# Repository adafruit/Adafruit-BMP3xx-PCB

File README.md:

## Adafruit BMP3xx - Precision Barometric Pressure and Altimeter PCB

<a href="http://www.adafruit.com/products/3966"><br/>
<a href="http://www.adafruit.com/products/3966"><br/>
<a href="http://www.adafruit.com/products/4816"><br/>
Click here to purchase one from the Adafruit shop</a>

PCB files for the Adafruit BMP388 - Precision Barometric Pressure and Altimeter. Format is EagleCAD schematic and board layout
* https://www.adafruit.com/product/3966
* https://www.adafruit.com/product/4816

### Description

Bosch has been a leader in barometric pressure sensors, from the [BMP085](https://www.adafruit.com/product/1603), [BMP180](https://www.adafruit.com/product/1603), and [BMP280](https://www.adafruit.com/product/2651)... now we've got the next generation, the **Adafruit BMP3xx Precision Barometric Pressure sensor**. As you would expect, this sensor is similar to its earlier versions but even better. The BMP388 has better precision than ever, which makes it excellent for environmental sensing or as a **precision altimeter**. It can even be used in either I2C and SPI configurations.

The BMP388 is the next-generation of sensors from Bosch, and is the upgrade to the BMP280 - with a low altitude noise as low as 0.1m and the same fast conversion time. And like the previous BMP280, you can use I2C or SPI. For simple easy wiring, go with I2C. If you want to connect a bunch of sensors without worrying about I2C address collisions, go with SPI.

The BMP390 is the next-generation of sensors from Bosch and is the upgrade to the BMP280 and BMP388 - with a low-altitude noise as low as 0.1m and the same fast conversion time. And like the previous BMP280, you can use I2C or SPI. For simple easy wiring, go with I2C. If you want to connect a bunch of sensors without worrying about I2C address collisions, go with SPI.

This sensor has a relative accuracy of 8 Pascals, which translates to about ± 0.5 meter of altitude (compare to the BMP280's 12 Pascal/ ±1 meter). The datasheet sort of implies they intend this sensor to be used for drones and quadcopters, to keep altitude stable, but you could also use this for wearables or any project that wants to track height-above-sea-level. Note that for absolute height you'll still need to enter in the barometric pressure at sea level, if the weather changes, but that's true of every altimeter sensor that uses pressure. You can also measure temperature with ±0.5°C accuracy.

Nice sensor right? So we made it easy for you to get right into your next project. The surface-mount sensor is soldered onto a PCB and comes with a 3.3V regulator and level shifting so you can use it with a 3V or 5V logic microcontroller without worry. [Check out the Arduino library to get data out in under 10 minutes!](https://github.com/adafruit/Adafruit_BMP3XX)

### License

Adafruit invests time and resources providing this open source design, please support Adafruit and open-source hardware by purchasing products from [Adafruit](https://www.adafruit.com)!

Designed by Limor Fried/Ladyada for Adafruit Industries.

Creative Commons Attribution/Share-Alike, all text above must be included in any redistribution. See license.txt for additional details.

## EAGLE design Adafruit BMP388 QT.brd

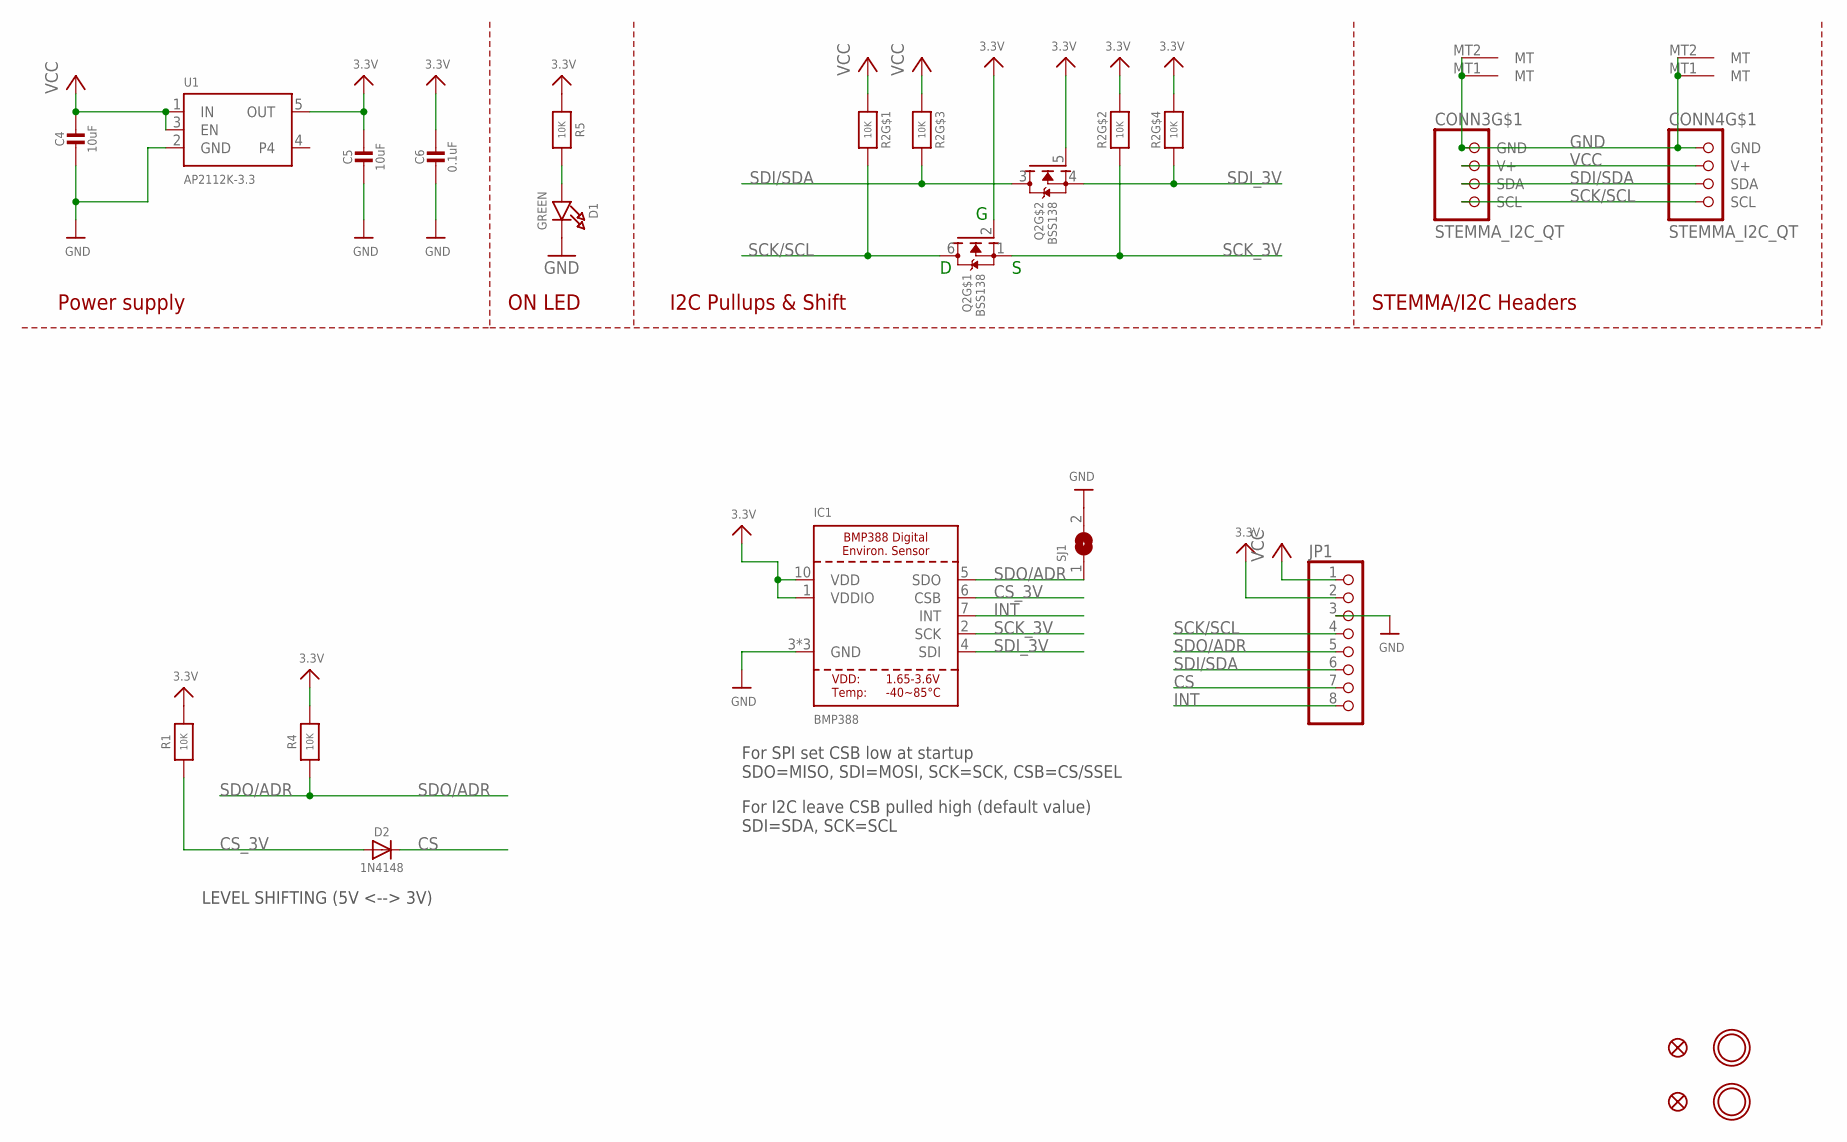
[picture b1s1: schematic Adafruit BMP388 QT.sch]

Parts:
C4, C5: 10uF; 0805-NO
C6: 0.1uF; 0603-NO
CONN3, CONN4: STEMMA_I2C_QT; JST_SH4
D1: GREEN; CHIPLED_0603_NOOUTLINE
D2: 1N4148; SOD-323
FID3, FID4: FIDUCIAL_1MM
IC1: BMP388
JP1: HEADER-1X870MIL; 1X08_ROUND_70
Q2: BSS138; SOT363
R1, R4, R5: 10K; 0603-NO
R2: 10K; RESPACK_4X0603
SJ1: SOLDERJUMPER; SOLDERJUMPER_ARROW_NOPASTE
U1: AP2112K-3.3; SOT23-5
U$40, U$41: MOUNTINGHOLE2.5; MOUNTINGHOLE_2.5_PLATED

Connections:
3.3V: C5.1, C6.1, IC1.1 (VDDIO), IC1.10 (VDD), JP1.2, Q2.2 (G), Q2.5 (G), R1.2, R2.2 (1), R2.4 (1), R4.2, R5.1, U1.5 (OUT)
CS: D2.C, JP1.7
CS_3V: D2.A, IC1.6 (CSB), R1.1
GND: C4.2, C5.2, C6.2, CONN3.1 (GND), CONN3.MT1 (MT), CONN3.MT2 (MT), CONN4.1 (GND), CONN4.MT1 (MT), CONN4.MT2 (MT), D1.C, IC1.3 (GND), IC1.8 (GND), IC1.9 (GND), JP1.3, SJ1.2, U1.2 (GND)
INT: IC1.7 (INT), JP1.8
unnamed: D1.A, R5.2
SCK/SCL: CONN3.4 (SCL), CONN4.4 (SCL), JP1.4, Q2.6 (D), R2.8 (2)
SCK_3V: IC1.2 (SCK), Q2.1 (S), R2.7 (2)
SDI/SDA: CONN3.3 (SDA), CONN4.3 (SDA), JP1.6, Q2.3 (D), R2.6 (2)
SDI_3V: IC1.4 (SDI), Q2.4 (S), R2.5 (2)
SDO/ADR: IC1.5 (SDO), JP1.5, R4.1, SJ1.1
VCC: C4.1, CONN3.2 (V+), CONN4.2 (V+), JP1.1, R2.1, R2.3 (1), U1.1 (IN), U1.3 (EN)

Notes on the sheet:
I2C Pullups & Shift
STEMMA/I2C Headers
ON LED
Power supply
For SPI set CSB low at startup SDO=MISO, SDI=MOSI, SCK=SCK, CSB=CS/SSEL
For I2C leave CSB pulled high (default value) SDI=SDA, SCK=SCL
LEVEL SHIFTING (5V <--> 3V)

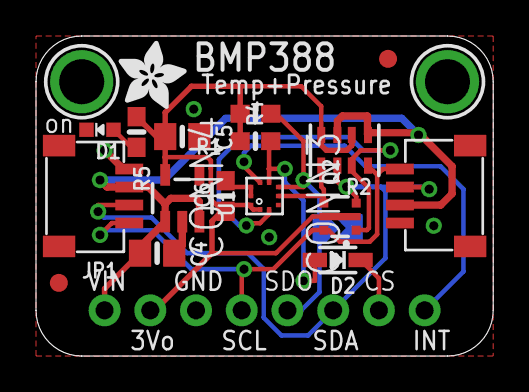
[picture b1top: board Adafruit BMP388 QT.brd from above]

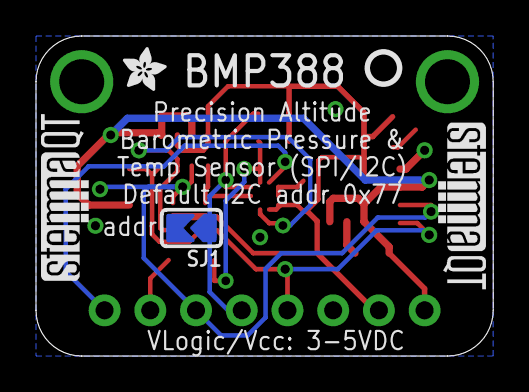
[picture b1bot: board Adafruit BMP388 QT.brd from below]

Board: 2 copper layers, 25.4 x 17.8 mm, 25 parts (5 on the bottom side), 12 nets.

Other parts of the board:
U$2: ADAFRUIT_2.5MM
U$46: ADAFRUIT_3.5MM
U$47: PCBFEAT-REV-040
U$48, U$49: STEMMAQT

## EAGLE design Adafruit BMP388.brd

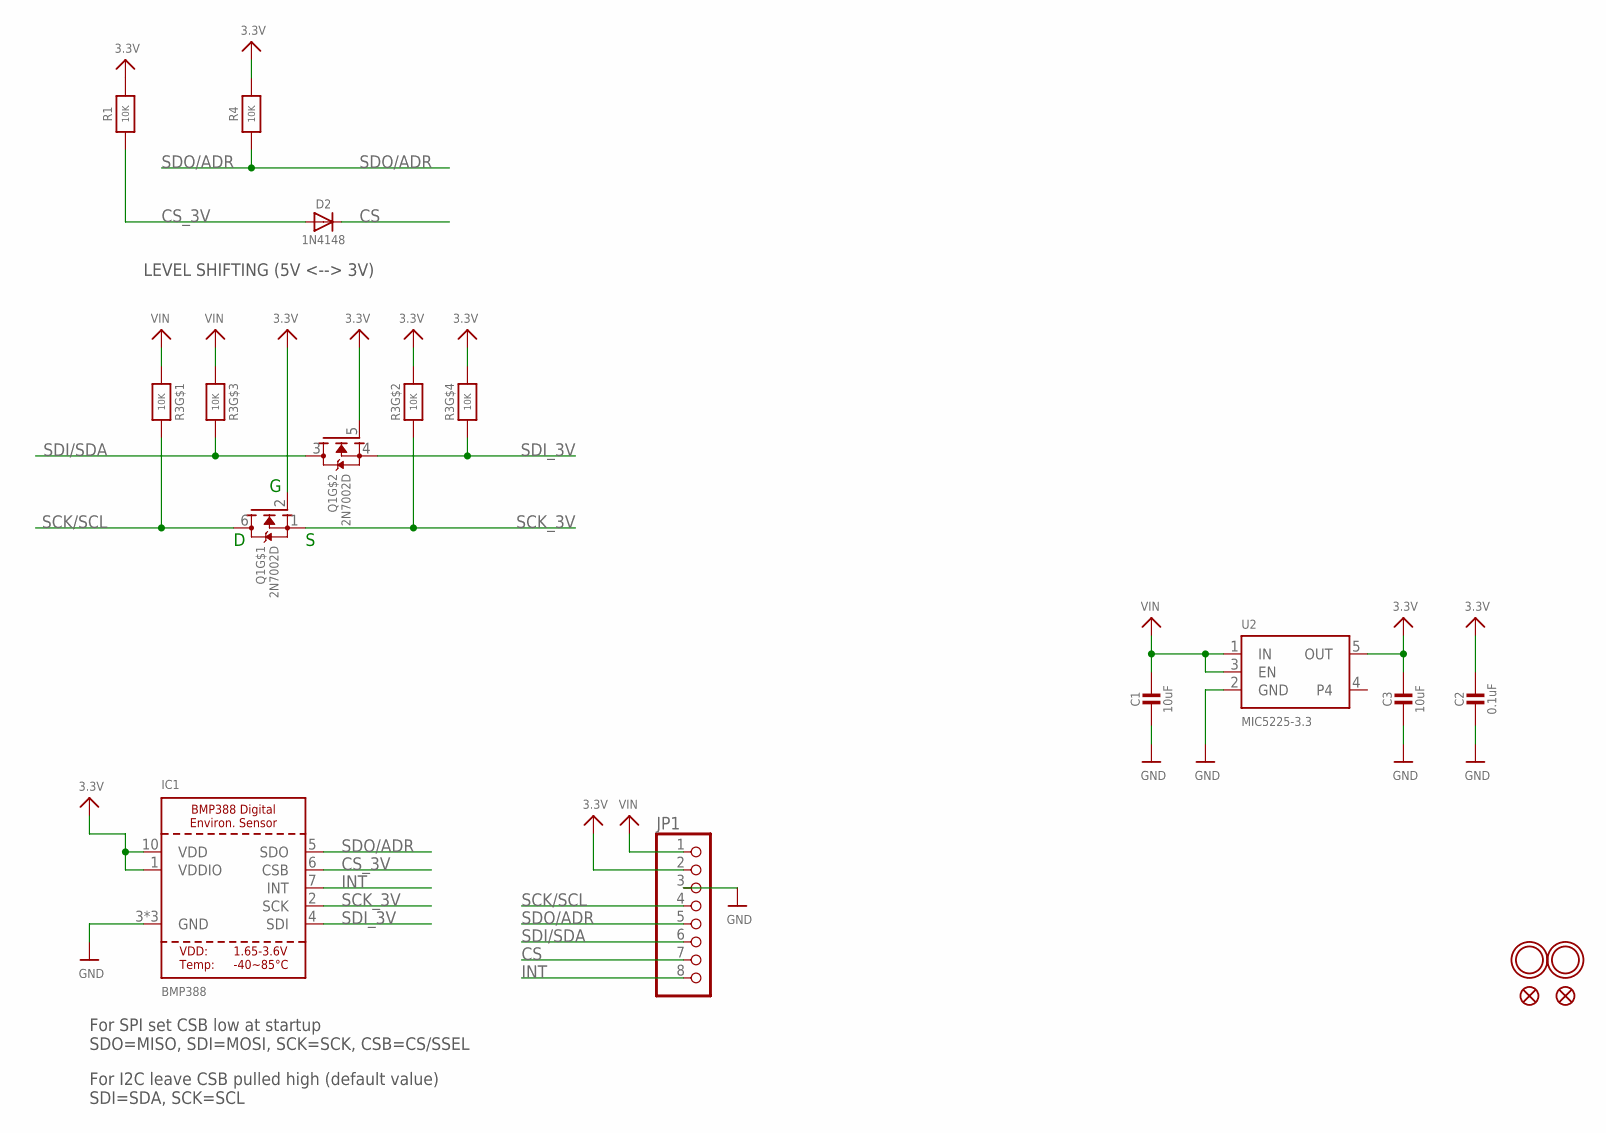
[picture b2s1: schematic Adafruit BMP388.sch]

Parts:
C1, C3: 10uF; 0805-NO
C2: 0.1uF; 0603-NO
D2: 1N4148; SOD-323
IC1: BMP388
JP1: HEADER-1X870MIL; 1X08_ROUND_70
Q1: 2N7002D; SOT363
R1, R4: 10K; 0603-NO
R3: 10K; RESPACK_4X0603
U2: MIC5225-3.3; SOT23-5
U$5, U$15: FIDUCIAL_1MM
U$7, U$8: MOUNTINGHOLE2.0; MOUNTINGHOLE_2.0_PLATED

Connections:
3.3V: C2.1, C3.1, IC1.1 (VDDIO), IC1.10 (VDD), JP1.2, Q1.2 (G), Q1.5 (G), R1.2, R3.2 (1), R3.4 (1), R4.2, U2.5 (OUT)
CS: D2.C, JP1.7
CS_3V: D2.A, IC1.6 (CSB), R1.1
GND: C1.2, C2.2, C3.2, IC1.3 (GND), IC1.8 (GND), IC1.9 (GND), JP1.3, U2.2 (GND)
INT: IC1.7 (INT), JP1.8
SCK/SCL: JP1.4, Q1.6 (D), R3.8 (2)
SCK_3V: IC1.2 (SCK), Q1.1 (S), R3.7 (2)
SDI/SDA: JP1.6, Q1.3 (D), R3.6 (2)
SDI_3V: IC1.4 (SDI), Q1.4 (S), R3.5 (2)
SDO/ADR: IC1.5 (SDO), JP1.5, R4.1
VIN: C1.1, JP1.1, R3.1, R3.3 (1), U2.1 (IN), U2.3 (EN)

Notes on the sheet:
For SPI set CSB low at startup SDO=MISO, SDI=MOSI, SCK=SCK, CSB=CS/SSEL
For I2C leave CSB pulled high (default value) SDI=SDA, SCK=SCL
LEVEL SHIFTING (5V <--> 3V)

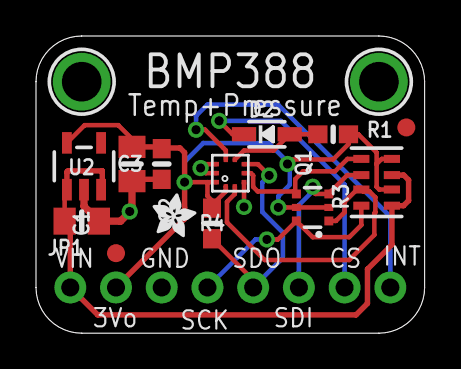
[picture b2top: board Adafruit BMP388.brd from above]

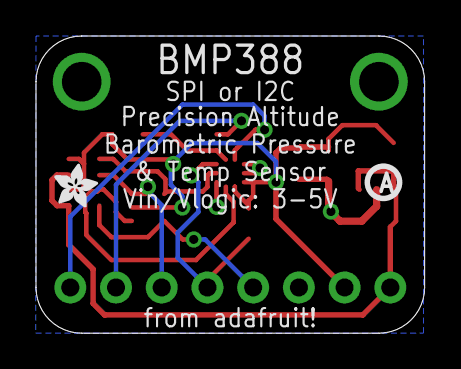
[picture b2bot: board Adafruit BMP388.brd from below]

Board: 2 copper layers, 21.6 x 16.5 mm, 18 parts (2 on the bottom side), 11 nets.

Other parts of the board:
U$2, U$6: ADAFRUIT_2.5MM
U$20: PCBFEAT-REV-040

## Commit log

2018-11-02 init!
2018-11-02 read it!
2019-07-16 updated to new pcb repo cookiecutter
2020-11-04 Add board files.
2020-11-04 Add image asset
2021-02-23 Add STEMMA asset
2021-02-23 Add asset
2021-02-23 Add board files
